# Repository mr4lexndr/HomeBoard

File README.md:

[![CC BY-NC-SA 4.0][cc-by-nc-sa-shield]][cc-by-nc-sa]

[![CC BY-NC-SA 4.0][cc-by-nc-sa-image]][cc-by-nc-sa]

This work is licensed under a
[Creative Commons Attribution-NonCommercial-ShareAlike 4.0 International License][cc-by-nc-sa].

[cc-by-nc-sa]: http://creativecommons.org/licenses/by-nc-sa/4.0/
[cc-by-nc-sa-image]: https://licensebuttons.net/l/by-nc-sa/4.0/88x31.png
[cc-by-nc-sa-shield]: https://img.shields.io/badge/License-CC%20BY--NC--SA%204.0-lightgrey.svg

# HomeBoard
Simple ESP32 based 4 Channel LV board for controlling Home appliances with [HomeSpan](https://github.com/HomeSpan/HomeSpan).
HomeBoard was created to controll variety of LED strips, and other Low voltage appliances. 

## Main Features
- Supply Voltage 3.5-30V
- Status LED and Control push button for easy configuration
- 4 PWM-eabled channels (0-Vin V, 25A)
- 2 channels can be configured with Logic Level Shifters to drive Neopixels etc.
- Switch or button option vailable.

## User Integration with HomeSpan
Status LED and Control Button are attached to deafault pins for most of the boards. S1 Button is also used as boot button during programming
- LED - GPIO2
- Button - GPIO0

## Variants
Four channels can be configured per requiremnts. Specific sections 1-3 has been marked on PCB. Only one group from each section should be soldered based on selected funtion. Available options:

| Channel | Main Function | Alternative |
| ------- | ------------- | ----------- |
| 1       | Open Drain    | Logic Level (0-Vin) |
| 2       | Open Drain    | Logic Level (0-Vin) |
| 3       | Open Drain    | Switch (GPIO18)     |
| 4       | Open Drain    | Switch (GND)        |

## TO DO

- 3D printed case
- update power circuit with more common IC
- update programming connector and decrease the size of the board

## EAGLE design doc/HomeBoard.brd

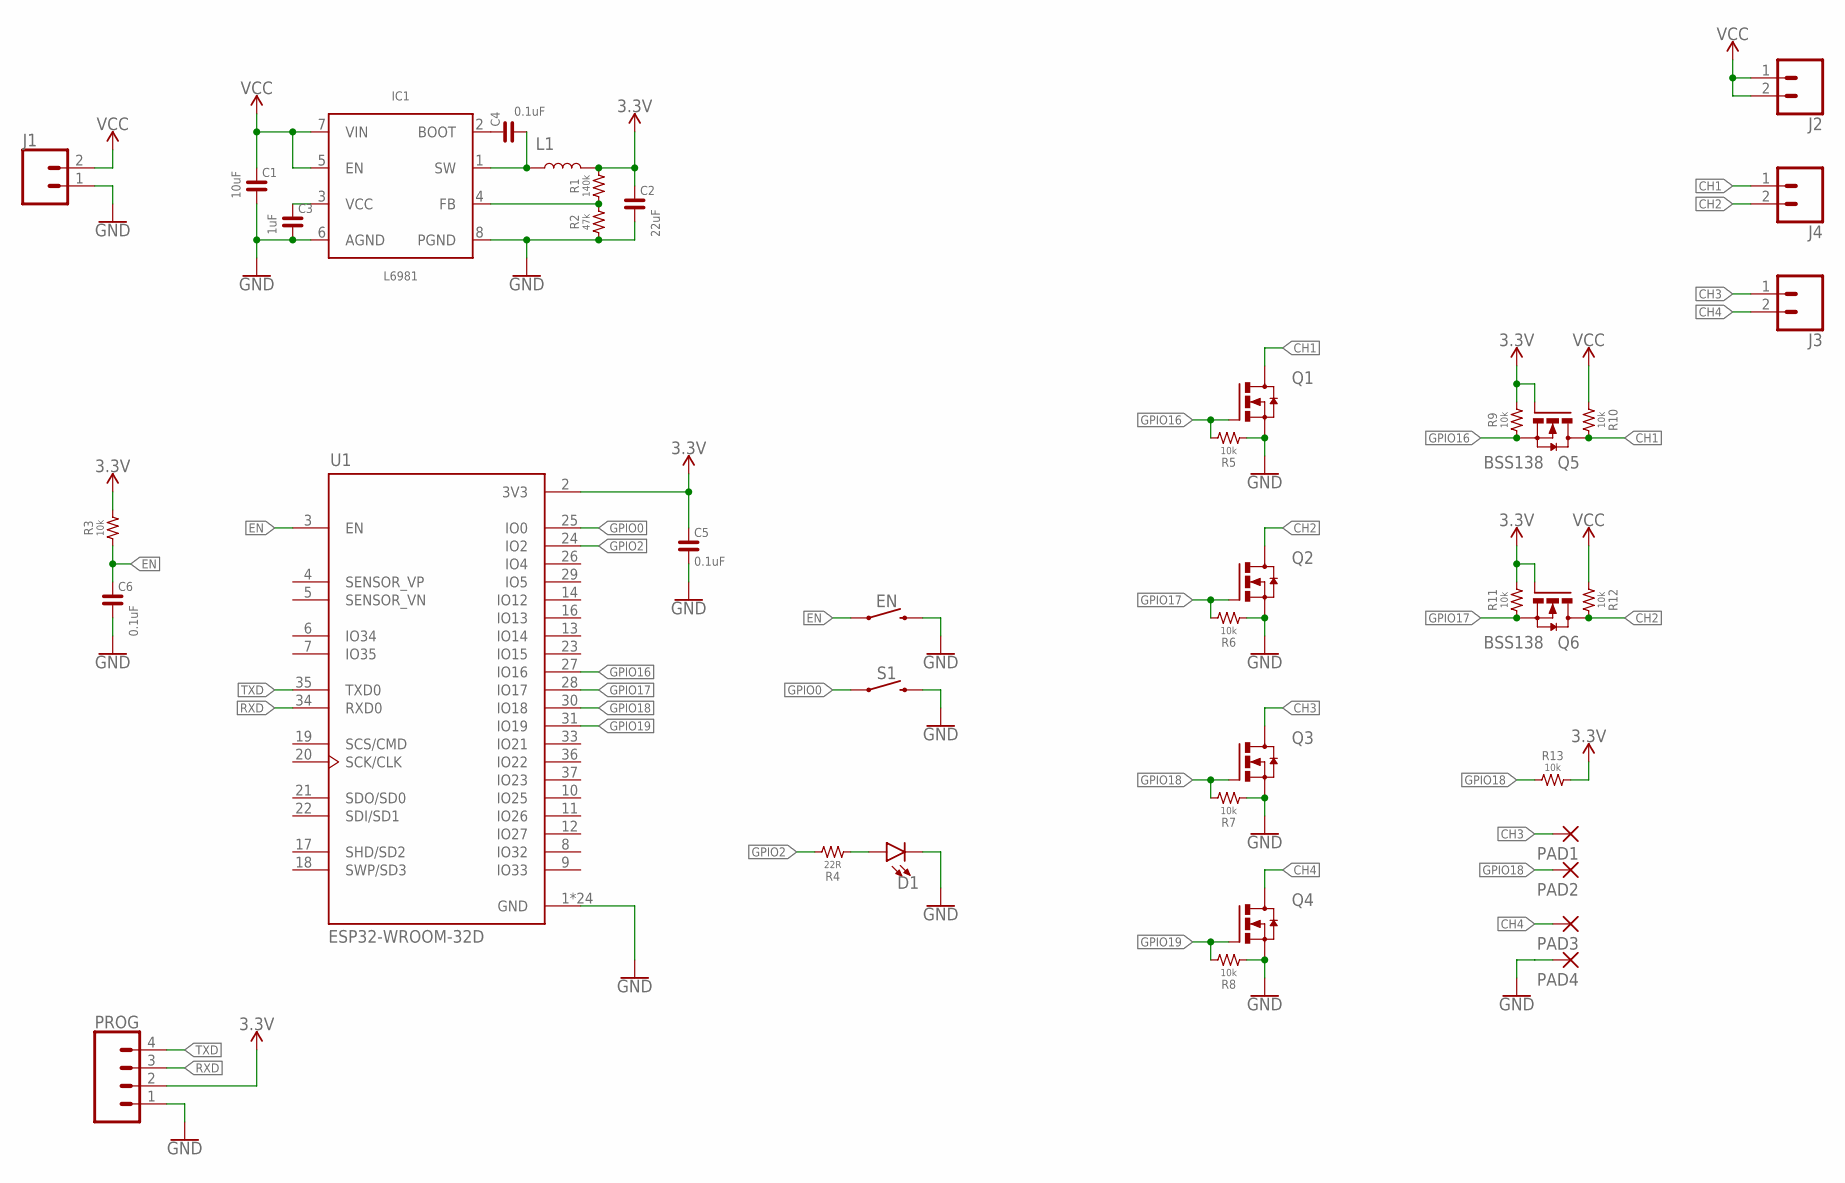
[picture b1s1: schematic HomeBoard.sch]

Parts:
C1: 10uF; 1206
C2: 22uF; 1206
C3: 1uF; 0603
C4, C5, C6: 0.1uF; 0603
D1: LED-ANGLE-2MM
EN: MOMENTARY-SWITCH-SPST-SMD-6.0X3.5MM; TACTILE_SWITCH_SMD_6.0X3.5MM
IC1: L6981; SO-8L
J1, J2, J3, J4: CONN_025MM; SCREWTERMINAL-5MM-2
L1: INDUCTOR-7.3X6.6
PAD1, PAD2, PAD3, PAD4: SMD_PADSMD-1X1.5MM; SMD1X1.5MM
PROG: CONN_04LOCK; 1X04_LOCK
Q1, Q2, Q3, Q4: MOSFET-N-DPAK; D-PAK_TO252AA
Q5, Q6: BSS138; SOT23-3
R1: 140k; 0603
R2: 47k; 0603
R3, R5, R6, R7, R8, R9, R10, R11, R12, R13: 10k; 0603
R4: 22R; 0603
S1: MOMENTARY-SWITCH-SPST-PTH-RIGHT-ANGLE-KIT; TACTILE_SWITCH_PTH_RIGHT_ANGLE_KIT
U1: ESP32-WROOM-32D; MODULE_ESP32-WROOM-32D

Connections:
3.3V: C2.2, C5.2, L1.P$2 (2), PROG.2, Q5.1 (G), Q6.1 (G), R1.2, R3.2, R9.2, R11.2, R13.2, U1.2 (3V3)
CH1: J4.1, Q1.4 (D), Q5.3 (D), R10.2
CH2: J4.2, Q2.4 (D), Q6.3 (D), R12.2
CH3: J3.1, PAD1.P$1, Q3.4 (D)
CH4: J3.2, PAD3.P$1, Q4.4 (D)
EN: C6.2, EN.1, R3.1, U1.3 (EN)
GND: C1.1, C2.1, C3.1, C5.1, C6.1, D1.C, EN.2, IC1.6 (AGND), IC1.8 (PGND), J1.1, PAD4.P$1, PROG.1, Q1.3 (S), Q2.3 (S), Q3.3 (S), Q4.3 (S), R2.1, R5.1, R6.1, R7.1, R8.1, S1.2, U1.1 (GND), U1.15 (GND), U1.38 (GND), U1.39_1 (GND), U1.39_2 (GND), U1.39_3 (GND), U1.39_4 (GND), U1.39_5 (GND), U1.39_6 (GND), U1.39_7 (GND), U1.39_8 (GND), U1.39_9 (GND), U1.39_10 (GND), U1.39_11 (GND), U1.39_12 (GND), U1.39_13 (GND), U1.39_14 (GND), U1.39_15 (GND), U1.39_16 (GND), U1.39_17 (GND), U1.39_18 (GND), U1.39_19 (GND), U1.39_20 (GND), U1.39_21 (GND)
GPIO0: S1.1, U1.25 (IO0)
GPIO2: R4.2, U1.24 (IO2)
GPIO16: Q1.1 (G), Q5.2 (S), R5.2, R9.1, U1.27 (IO16)
GPIO17: Q2.1 (G), Q6.2 (S), R6.2, R11.1, U1.28 (IO17)
GPIO18: PAD2.P$1, Q3.1 (G), R7.2, R13.1, U1.30 (IO18)
GPIO19: Q4.1 (G), R8.2, U1.31 (IO19)
unnamed: IC1.4 (FB), R1.1, R2.2
unnamed: C4.1, IC1.1 (SW), L1.P$1 (1)
unnamed: C4.2, IC1.2 (BOOT)
unnamed: D1.A, R4.1
unnamed: C3.2, IC1.3 (VCC)
RXD: PROG.3, U1.34 (RXD0)
TXD: PROG.4, U1.35 (TXD0)
VCC: C1.2, IC1.5 (EN), IC1.7 (VIN), J1.2, J2.1, J2.2, R10.1, R12.1

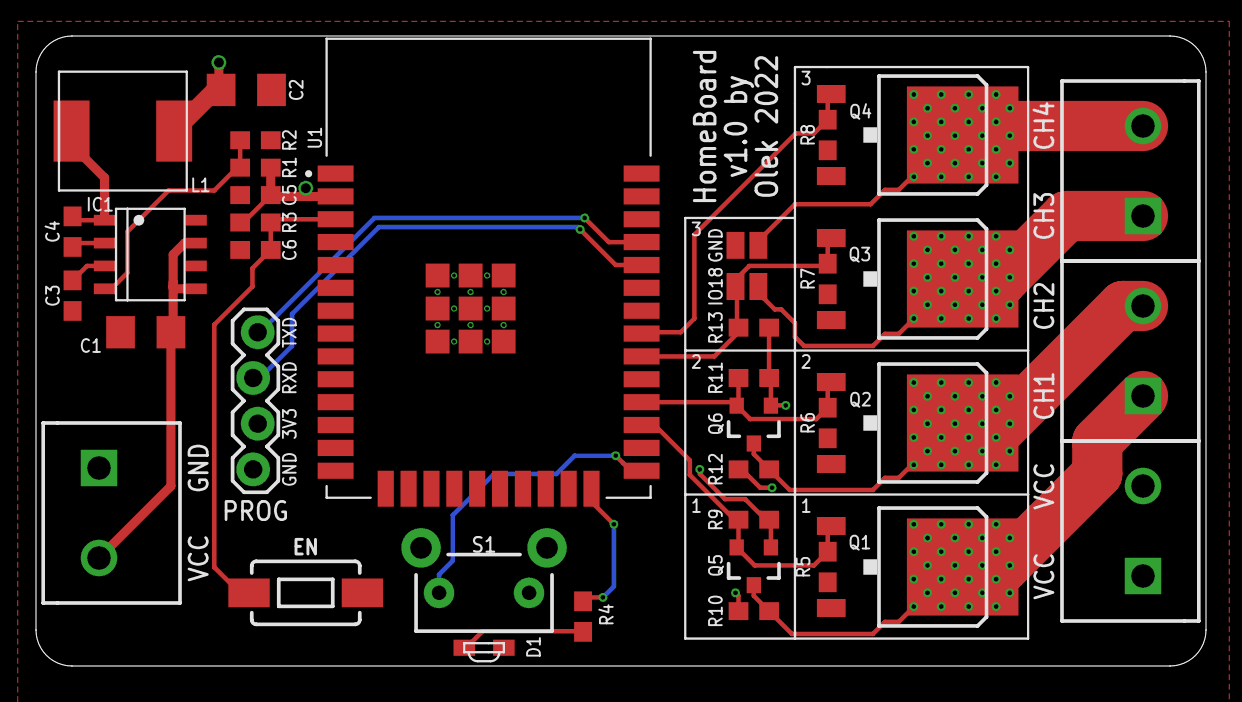
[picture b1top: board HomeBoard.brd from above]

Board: 2 copper layers, 65.0 x 35.0 mm, 40 parts (0 on the bottom side), 21 nets.

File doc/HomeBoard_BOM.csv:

Qty,Value,Device,Package,Parts,Description
4,,CONN_025MM,SCREWTERMINAL-5MM-2,"J1, J2, J3, J4",Multi connection point. Often used as Generic Header-pin footprint for 0.1 inch spaced/style header connections
1,,CONN_04LOCK,1X04_LOCK,PROG,Multi connection point. Often used as Generic Header-pin footprint for 0.1 inch spaced/style header connections
1,,INDUCTOR-7.3X6.6,INDUCTOR-7.3X6.6,L1,Inductor
4,,MOSFET-N-DPAK,D-PAK_TO252AA,"Q1, Q2, Q3, Q4",N-Channel MOSFET in various packages
3,0.1uF,CAP-0603,0603,"C4, C5, C6",
10,10k,RESISTOR0603,0603,"R3, R5, R6, R7, R8, R9, R10, R11, R12, R13",Generic Resistor Package
1,10uF,CAP-1206,1206,C1,
1,140k,RESISTOR0603,0603,R1,Generic Resistor Package
1,1uF,CAP-0603,0603,C3,
1,22R,RESISTOR0603,0603,R4,Generic Resistor Package
1,22uF,CAP-1206,1206,C2,
1,47k,RESISTOR0603,0603,R2,Generic Resistor Package
2,BSS138,MOSFET-N-SOT23-3,SOT23-3,"Q5, Q6",N-Channel MOSFET in various packages
1,ESP32-WROOM-32D,ESP32-WROOM-32D,MODULE_ESP32-WROOM-32D,U1,"Bluetooth, WiFi 802.11b/g/n, Bluetooth v4.2 + EDR, Class 1, 2 and 3 Transceiver Module 2.4GHz ~ 2.5GHz Integrated, Trace Surface Mount Check prices"
1,L6981,L6981,SO-8L,IC1,"L6981 38 V, 1.5 A synchronous step-down converter"
1,LTST-S220TBKT,LED-ANGLE-2MM,LED-ANGLE-2MM,D1,LED (Generic)
1,MOMENTARY-SWITCH-SPST-PTH-RIGHT-ANGLE-KIT,MOMENTARY-SWITCH-SPST-PTH-RIGHT-ANGLE-KIT,TACTILE_SWITCH_PTH_RIGHT_ANGLE_KIT,S1,Momentary Switch (Pushbutton) - SPST
1,MOMENTARY-SWITCH-SPST-SMD-6.0X3.5MM,MOMENTARY-SWITCH-SPST-SMD-6.0X3.5MM,TACTILE_SWITCH_SMD_6.0X3.5MM,EN,Momentary Switch (Pushbutton) - SPST

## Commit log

2022-03-14 Create LICENSE
2022-03-14 Rename LICENSE to LICENSE.md
2022-03-15 Images
2022-03-15 Eagle files
2022-03-15 Fusion File
2022-03-15 Updated images
2022-03-16 updated1603

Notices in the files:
parts and their libraries:
SparkFun-PowerSymbols: Licensing: Creative Commons ShareAlike 4.0 International - https://creativecommons.org/licenses/by-sa/4.0
